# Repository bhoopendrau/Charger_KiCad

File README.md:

# Charger_KiCad
##### Open source Mobile charge PCB design Made for a college assignment.

Charger Specs
1. Dual usb out
2. max 2.1Amp current per USB
3. 15 w max output

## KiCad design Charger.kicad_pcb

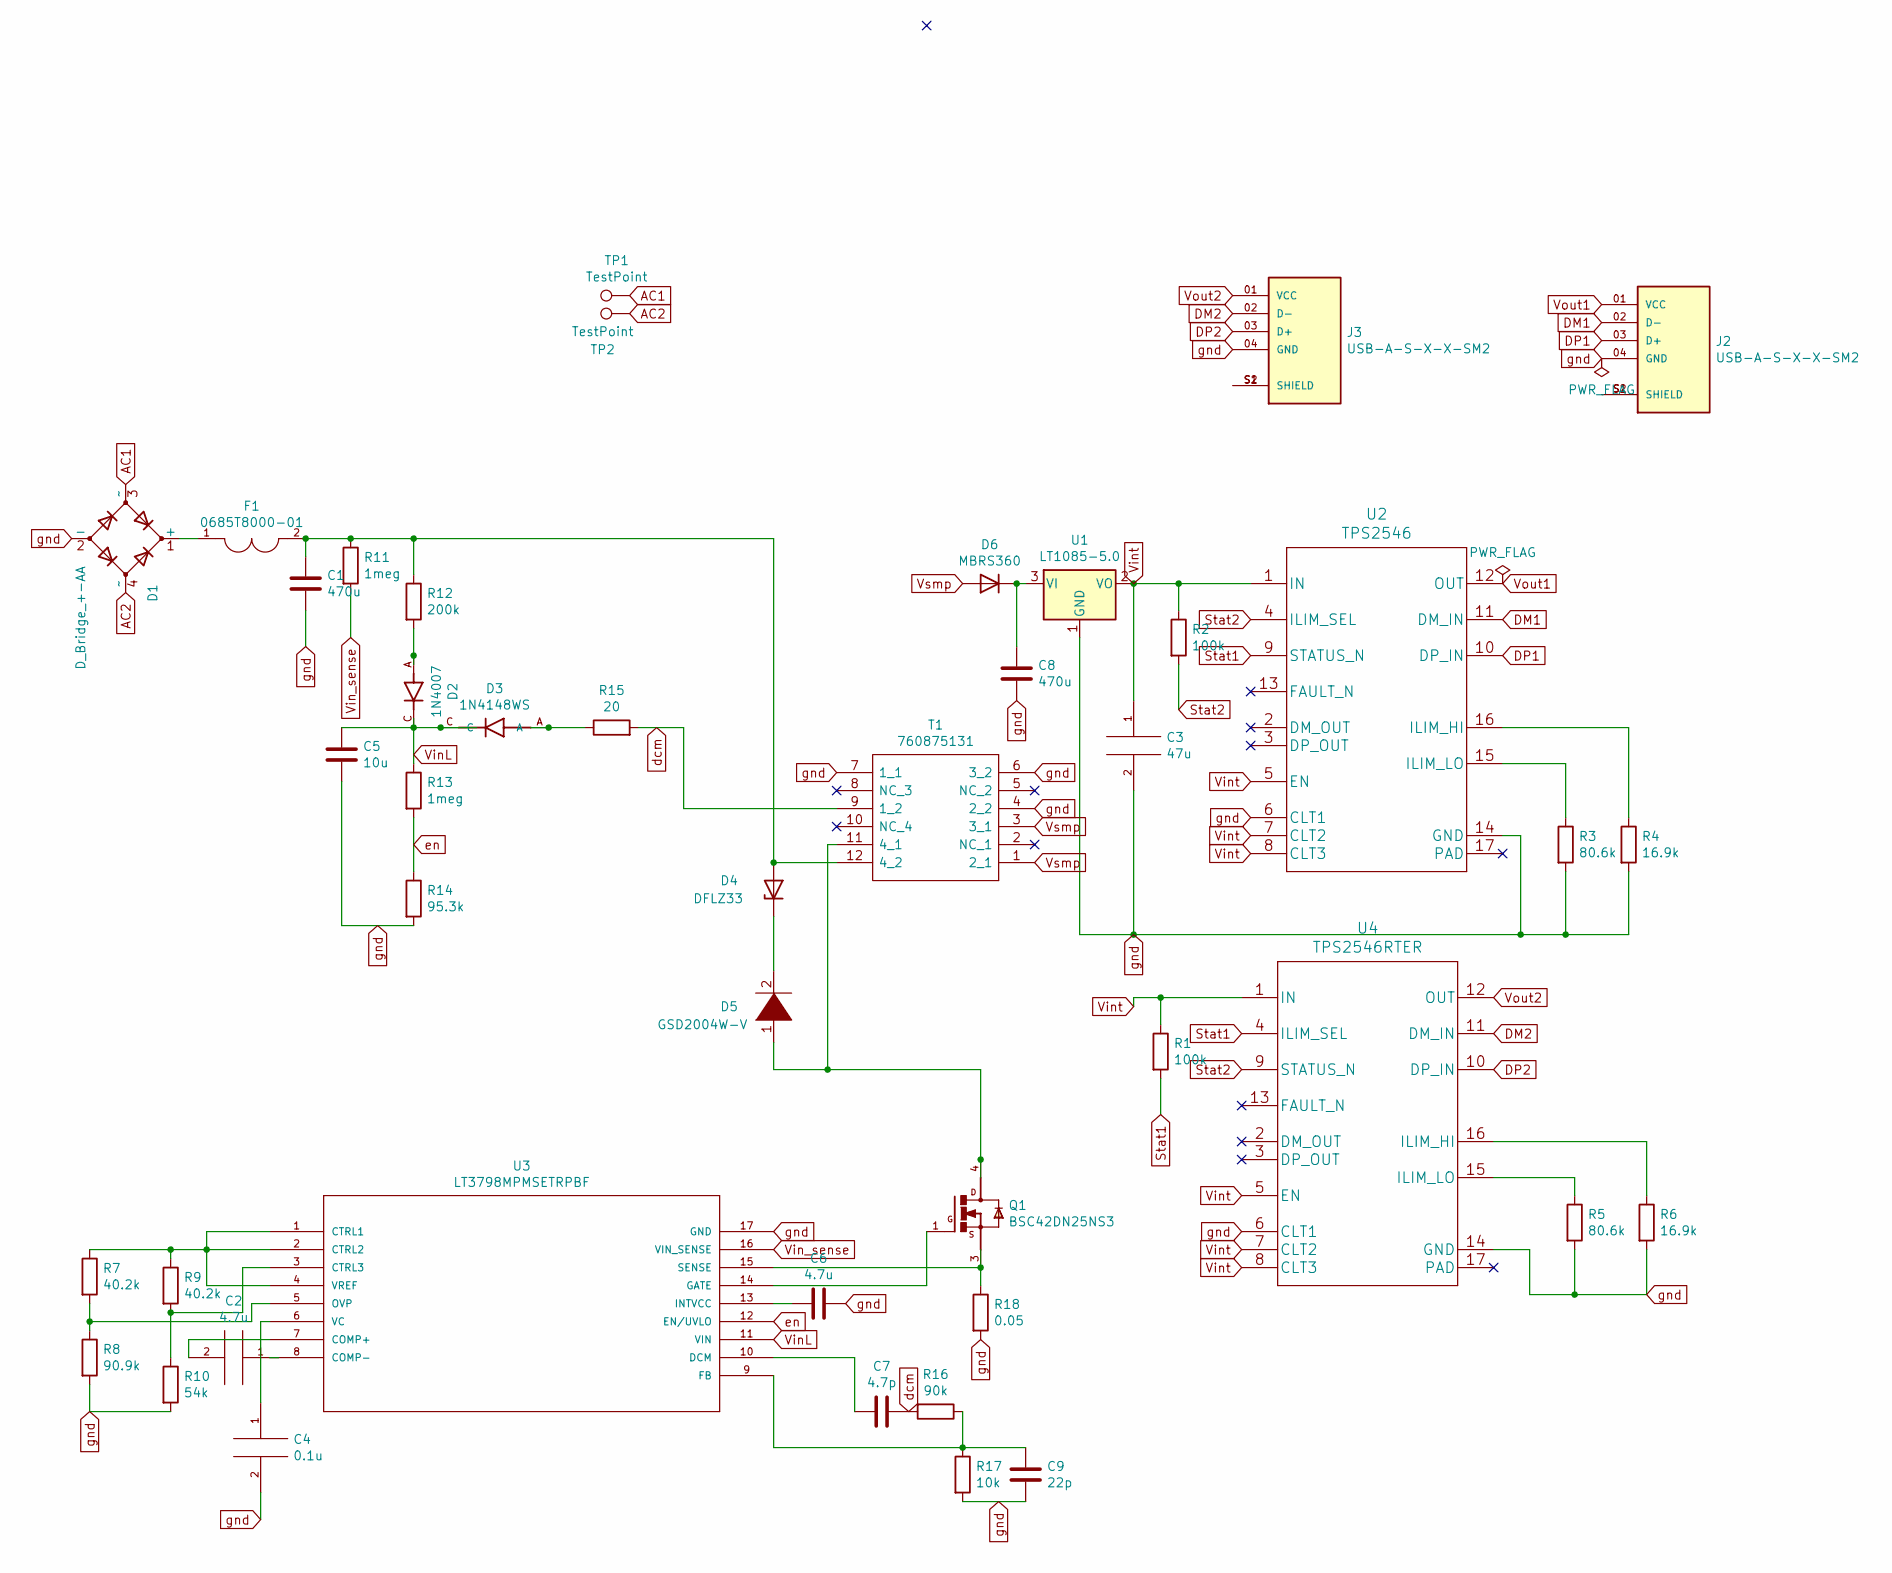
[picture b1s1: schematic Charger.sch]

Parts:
C1, C8: 470u; CP_Elec_5x4.4
C2, C6: 4.7u; CAPC2012X140N
C3: 47u; CP_Elec_4x3.9
C4: 0.1u; CP_Elec_3x5.3
C5: 10u; CP_Elec_3x5.3
C7: 4.7p; CP_Elec_3x5.3
C9: 22p; CP_Elec_3x5.3
D1: D_Bridge_+-AA; SOIC245P670X270-4N
D2: 1N4007; DIOAD1060W80L520D270; PARTREV G
D3: 1N4148WS; SODFL2512X100N
D4: DFLZ33; D_1812_4532Metric_Pad1.30x3.40mm_HandSolder
D5: GSD2004W-V; D_1812_4532Metric_Pad1.30x3.40mm_HandSolder
D6: MBRS360; D_1812_4532Metric_Pad1.30x3.40mm_HandSolder
F1: 0685T8000-01; FUSC3215X83N; PARTREV Jan2019
J2, J3: USB-A-S-X-X-SM2; SAMTEC_USB-A-S-X-X-SM2; PARTREV T
Q1: BSC42DN25NS3; SOT230P700X180-4N
R1, R2: 100k; RESC1005X40N
R3, R5: 80.6k; RESC5025X70N
R4, R6: 16.9k; RESC1608X50N
R7, R9: 40.2k; RESC1608X50N
R8: 90.9k; RESC5025X70N
R10: 54k; RESC5025X70N
R11, R13: 1meg; RESC2012X65N
R12: 200k; RESC1005X40N
R14: 95.3k; RESC1005X40N
R15: 20; RESC1005X35N
R16: 90k; RESC5025X70N
R17: 10k; RESC1608X50N
R18: 0.05; RESC1005X35N
T1: 760875131; Manufacturer_Part_Number 760875131; Mouser Part Number 710-760875131
TP1, TP2: TestPoint; TestPoint_Pad_2.0x2.0mm
U1: LT1085-5.0; TO220L1
U2: TPS2546; TPS2546RTER
U3: LT3798MPMSETRPBF; MSOP-16_MSE; MANUFACTURER_PART_NUMBER lt3798mpmse#trpbf
U4: TPS2546RTER

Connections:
AC1: D1.3 (~~), TP1.1
AC2: D1.4 (~~), TP2.1
DM1: J2.02 (D-), U2.11 (DM_IN)
DM2: J3.02 (D-), U4.11 (DM_IN)
DP1: J2.03 (D+), U2.10 (DP_IN)
DP2: J3.03 (D+), U4.10 (DP_IN)
unnamed: C1.1, D4.2 (A), F1.2, R11.1, R12.1, T1.12 (4_2)
unnamed: C2.1, U3.8 (COMP-)
unnamed: C2.2, U3.7 (COMP+)
unnamed: C4.1, U3.6 (VC)
unnamed: C6.1, U3.13 (INTVCC)
unnamed: C7.2, U3.10 (DCM)
unnamed: C8.1, D6.1 (K), U1.3 (VI)
unnamed: C9.1, R16.1, R17.1, U3.9 (FB)
unnamed: D1.1 (+), F1.1
unnamed: D2.A, R12.2
unnamed: D3.A, R15.1
unnamed: D4.1 (K), D5.2 (A)
unnamed: D5.1 (K), Q1.4, T1.11 (4_1)
unnamed: J2.S1 (SHIELD), J2.S2 (SHIELD)
unnamed: J3.S1 (SHIELD), J3.S2 (SHIELD)
unnamed: Q1.1, U3.14 (GATE)
unnamed: Q1.3, R18.1, U3.15 (SENSE)
unnamed: R3.1, U2.15 (ILIM_LO)
unnamed: R4.1, U2.16 (ILIM_HI)
unnamed: R5.1, U4.15 (ILIM_LO)
unnamed: R6.1, U4.16 (ILIM_HI)
unnamed: R7.1, R9.1, U3.1 (CTRL1), U3.2 (CTRL2), U3.4 (VREF)
unnamed: R7.2, R8.1, U3.5 (OVP)
unnamed: R9.2, R10.1, U3.3 (CTRL3)
Stat1: R1.2, U2.9 (STATUS_N), U4.4 (ILIM_SEL)
Stat2: R2.2, U2.4 (ILIM_SEL), U4.9 (STATUS_N)
VinL: C5.1, D2.C, D3.C, R13.1, U3.11 (VIN)
Vin_sense: R11.2, U3.16 (VIN_SENSE)
Vint: C3.1, R1.1, R2.1, U1.2 (VO), U2.1 (IN), U2.5 (EN), U2.7 (CLT2), U2.8 (CLT3), U4.1 (IN), U4.5 (EN), U4.7 (CLT2), U4.8 (CLT3)
Vout1: J2.01 (VCC), U2.12 (OUT)
Vout2: J3.01 (VCC), U4.12 (OUT)
Vsmp: D6.2 (A), T1.1 (2_1), T1.3 (3_1)
dcm: C7.1, R15.2, R16.2, T1.9 (1_2)
en: R13.2, R14.1, U3.12 (EN/UVLO)
gnd: C1.2, C3.2, C4.2, C5.2, C6.2, C8.2, C9.2, D1.2 (-), J2.04 (GND), J3.04 (GND), R3.2, R4.2, R5.2, R6.2, R8.2, R10.2, R14.2, R17.2, R18.2, T1.4 (2_2), T1.6 (3_2), T1.7 (1_1), U1.1 (GND), U2.6 (CLT1), U2.14 (GND), U3.17 (GND), U4.6 (CLT1), U4.14 (GND)

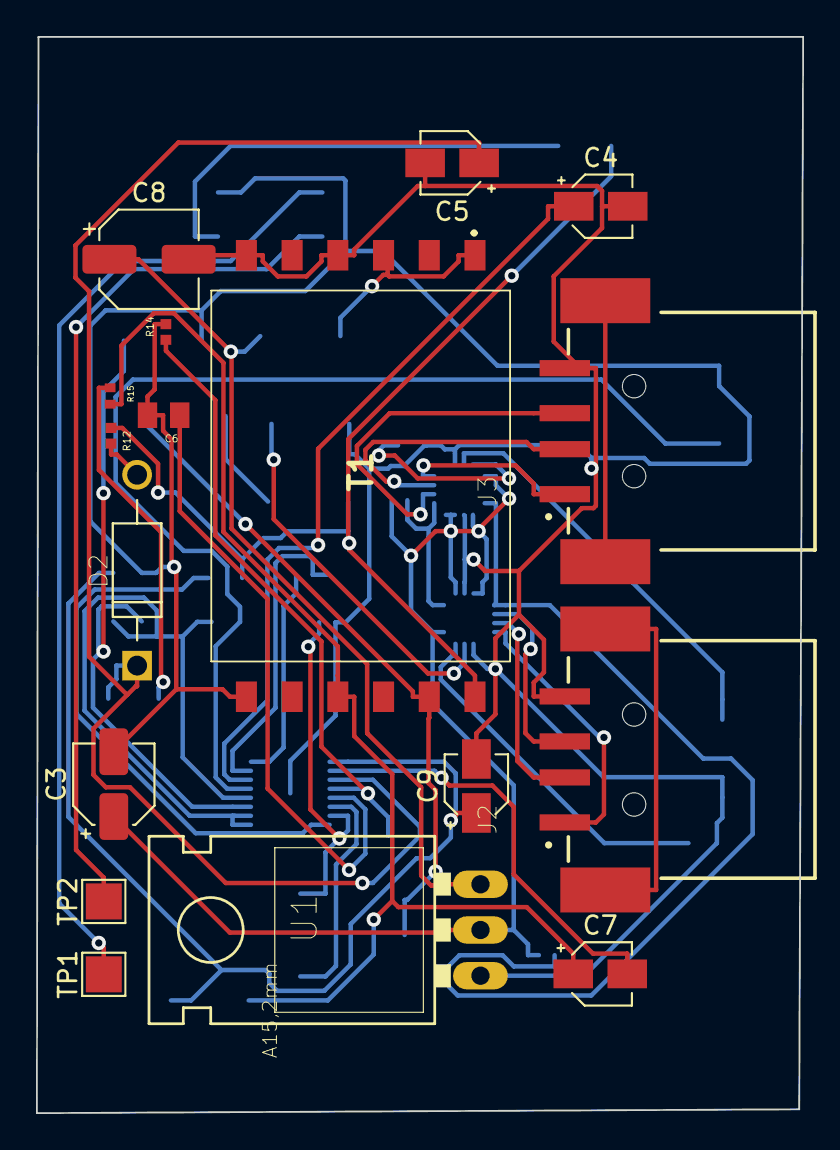
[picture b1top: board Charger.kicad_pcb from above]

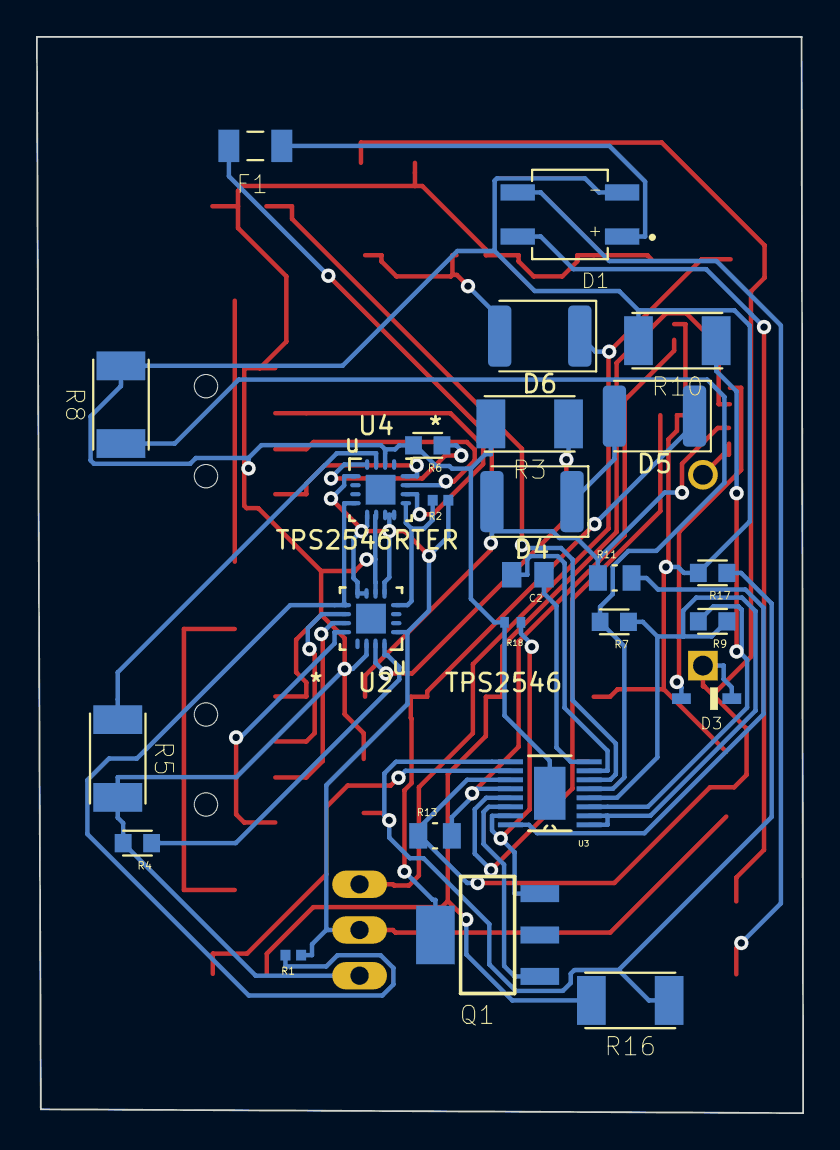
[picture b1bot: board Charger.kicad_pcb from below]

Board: 2 copper layers, 42.6 x 59.8 mm, 43 parts (26 on the bottom side), 41 nets.

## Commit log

2021-02-20 added two resistor
2021-02-20 changed location of files
2021-02-20 added ckt
2021-02-20 schematics updated
2021-02-20 pcb designed
2021-02-20 major changes
2021-02-20 actual components added
2021-02-21 footprints repaired
2021-02-21 3d view edited
2021-02-21 3d view updated
2021-02-22 usb controller added
2021-02-23 improved schematics
2021-02-23 updates schematics
2021-02-23 minor updates
2021-02-23 just pcb update
2021-02-24 newer schematics
2021-02-24 added components
2021-02-24 updatr
2021-02-24 SMP connections done
    stat inputs of 2546 corrected
    smp circuit connections done
    diode, mosfet models remaining
    internal resistance of capacitance remaining
    transformer remaining
2021-02-25 schematics completed
2021-02-25 footprint added
2021-02-25 transformer footprint added
2021-02-25 footprints finalised
2021-02-25 routing done
2021-02-25 completed (i think)
2021-02-25 some errors in pcb mitigated
2021-02-26 compact
2021-02-27 added fuse
2021-03-05 updated size
2021-03-13 final

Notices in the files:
parts and their libraries:
Copyright 2016 Accelerated Designs. All rights reserved.
